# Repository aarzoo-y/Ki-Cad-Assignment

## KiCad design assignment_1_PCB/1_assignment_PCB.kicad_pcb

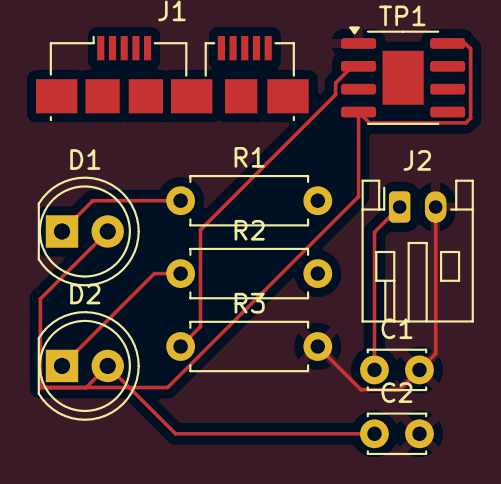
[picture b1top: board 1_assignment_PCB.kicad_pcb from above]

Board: 2 copper layers, 10 parts (0 on the bottom side), 8 nets.

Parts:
C1, C2: 10 uf; C_Disc_D3.0mm_W2.0mm_P2.50mm
D1, D2: LED; LED_D5.0mm
J1: USB_C_Receptacle_PowerOnly_6P; USB3_Micro-B_Connfly_DS1104-01
J2: Conn_01x02_Pin; JST_PH_S2B-PH-K_1x02_P2.00mm_Horizontal
R1, R2: 100; R_Axial_DIN0207_L6.3mm_D2.5mm_P7.62mm_Horizontal
R3: 10k; R_Axial_DIN0207_L6.3mm_D2.5mm_P7.62mm_Horizontal
TP1: SOIC-8-1EP_3.9x4.9mm_P1.27mm_EP2.29x3mm

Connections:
GND: C1.2, C2.2, J2.2, R3.2, TP1.1 (TEMP), TP1.3 (GND)
unnamed: D1.1 (K), R1.1
unnamed: D2.1 (K), R2.1
unnamed: R1.2, TP1.7 (CHRG)
unnamed: R3.1, TP1.2 (PROG)
unnamed: R2.2, TP1.5 (STDBY)
VCC: C2.1, D1.2 (A), D2.2 (A), TP1.4 (Vcc), TP1.8 (CE)
VD: C1.1, J2.1

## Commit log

2025-05-27 Create random
